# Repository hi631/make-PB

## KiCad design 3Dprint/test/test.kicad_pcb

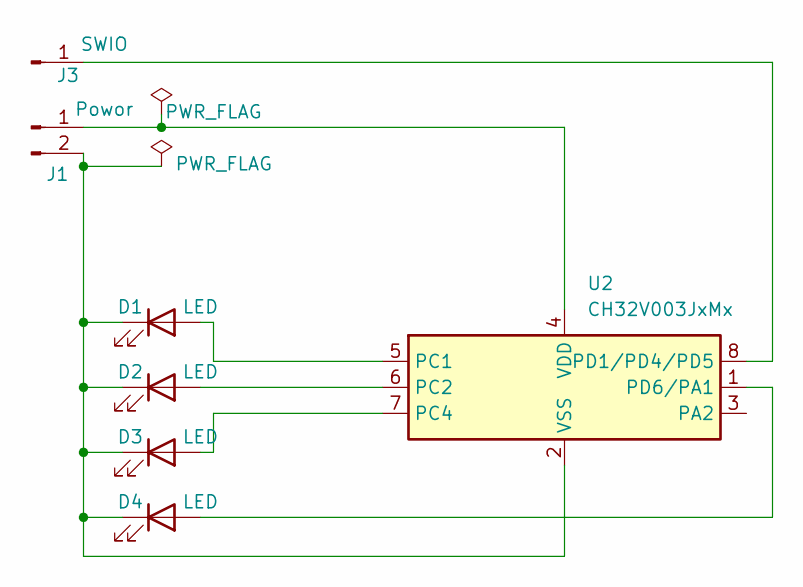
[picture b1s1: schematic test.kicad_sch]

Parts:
D1, D2, D3, D4: LED; LED_0805_2012Metric
J1: Powor; PinHeader_1x02_P2.54mm_Vertical
J3: SWIO; PinSocket_1x01_P1.27mm_Vertical
U2: CH32V003JxMx; JEITA_SOIC-8_3.9x4.9mm_P1.27mm

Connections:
unnamed: D1.2 (A), U2.5 (PC1)
unnamed: D1.1 (K), D2.1 (K), D3.1 (K), D4.1 (K), J1.2, U2.2 (VSS)
unnamed: D2.2 (A), U2.6 (PC2)
unnamed: D3.2 (A), U2.7 (PC4)
unnamed: D4.2 (A), U2.1 (PD6/PA1)
unnamed: J1.1, U2.4 (VDD)
unnamed: J3.1 (Pin_1_1), U2.8 (PD1/PD4/PD5)

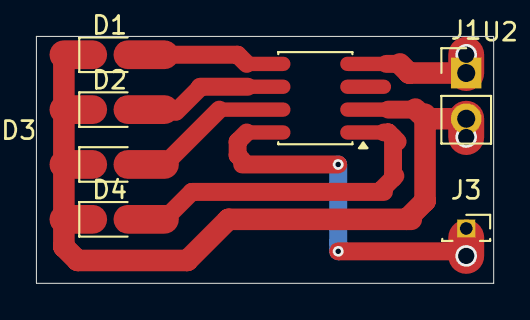
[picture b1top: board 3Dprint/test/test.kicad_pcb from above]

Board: 2 copper layers, 25.4 x 13.7 mm, 7 parts (0 on the bottom side), 7 nets.

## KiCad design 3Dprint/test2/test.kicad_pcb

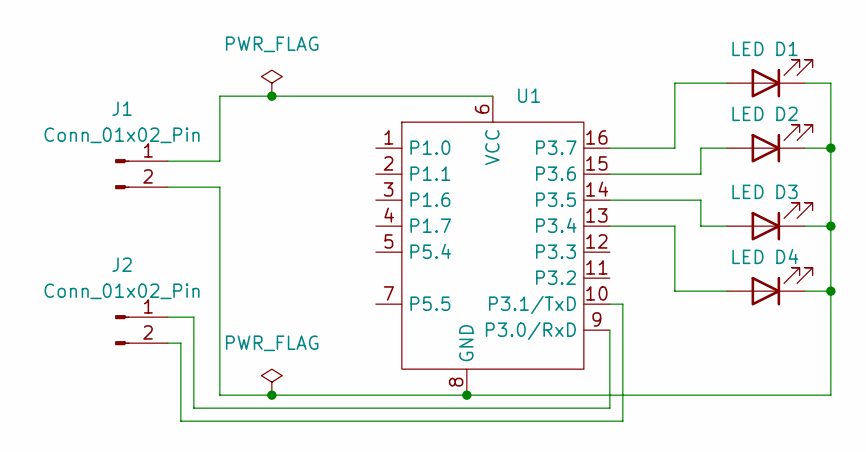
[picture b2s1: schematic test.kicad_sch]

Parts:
D1, D2, D3, D4: LED; LED_D3.0mm_Horizontal_O1.27mm_Z2.0mm
J1, J2: Conn_01x02_Pin; PinHeader_1x02_P2.54mm_Vertical
U1: DIP-16_W7.62mm

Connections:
unnamed: D1.2 (A), U1.16 (P3.7)
unnamed: D1.1 (K), D2.1 (K), D3.1 (K), D4.1 (K), J1.2, U1.8 (GND)
unnamed: D2.2 (A), U1.15 (P3.6)
unnamed: D3.2 (A), U1.14 (P3.5)
unnamed: D4.2 (A), U1.13 (P3.4)
unnamed: J1.1, U1.6 (VCC)
unnamed: J2.1, U1.9 (P3.0/RxD)
unnamed: J2.2, U1.10 (P3.1/TxD)

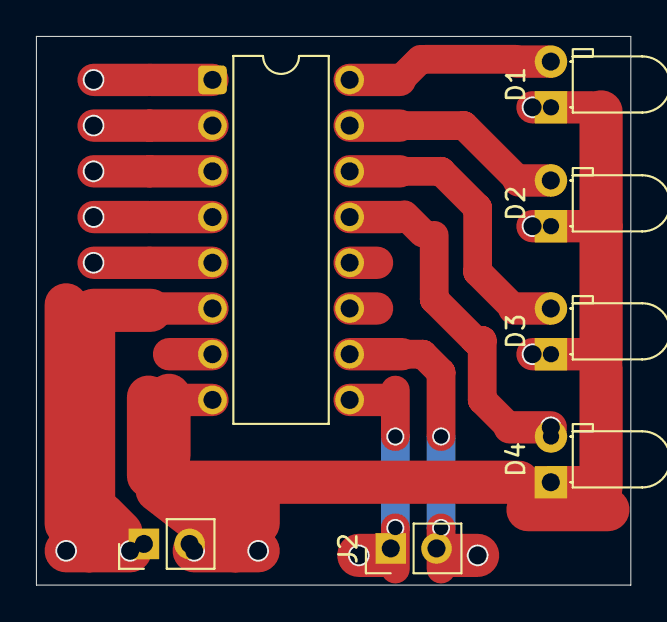
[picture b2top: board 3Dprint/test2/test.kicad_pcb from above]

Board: 2 copper layers, 33.0 x 30.5 mm, 7 parts (0 on the bottom side), 8 nets.

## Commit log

2018-11-07 test
2026-06-13 new 2026/06/13
